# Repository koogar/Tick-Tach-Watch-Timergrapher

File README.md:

## Tick-Tach: A DIY Timegrapher for Watch Enthusiasts - TallmanLabs 2025

  Mechanical watches may seem timeless, but keeping them accurate requires precise adjustment. That’s where a timegrapher comes in. Traditionally a tool for professional watchmakers, a timegrapher measures the tiny variations in a watch’s ticking to reveal how well its movement is performing.

%20(Large).jpg)
%20(Large).jpg)

## What a Timegrapher Does

At its core, a timegrapher listens to the tick-tock of a mechanical watch and turns that sound into data. The key readings are:

  * Rate – how many seconds the watch gains or loses per day.

  * Amplitude – the swing of the balance wheel, an indicator of movement power.

  * Beat Error – how evenly spaced the tick and tock are, showing whether the balance is centred.

  Together, these measurements tell whether a watch is healthy, in need of regulation, or due for service.

https://github.com/user-attachments/assets/4d9fce35-94cd-408c-842e-20433776a29b

## The Tick-Tach Approach

  Tick-Tach is a DIY project that recreates the essential functions of a timegrapher using simple, accessible parts. Instead of an expensive acoustic sensor, Tick-Tach relies on a 30mm piezo electric microphone to detect the faint vibrations of a watch. The weak signal is amplified with a transistor-based preamp before being processed into meaningful timing data.

  Unlike commercial probes, Tick-Tach’s electronics are housed in a custom 3D-printed enclosure. The case (shown above) is designed with a circular recess for the watch to rest on, a cavity for the 30mm piezo sensor, a neatly integrated preamp board, and a headphone-style jack for easy connection. A small toggle switch adds convenience. A hair bobble is integrated into the case to retain the watch when rotating, during different position tests.

Tick-Tach is also software compatible, working with the open-source “tg-timer”, "PC Timer Machine" application on PC and the "Watch Accuracy Meter" app on Android. This allows users to visualise live waveforms, track performance, and adjust their watches using the platform they prefer.

## Why It Matters

  For hobbyists, modders, and independent watch repairers, commercial timegraphers can be costly. Tick-Tach lowers the barrier, offering enthusiasts a practical way to check accuracy, regulate their watches, and better understand the mechanics inside. It’s also a rewarding build for anyone into electronics, 3D printing, and horology.

With its smart enclosure and open-source software compatibility, Tick-Tach bridges the gap between professional watchmaking tools and the DIY workshop.

.png)

%20(Large).jpg)

%20(Large).jpg)

%20(Large).jpg)

## Technical Notes & Tips

* Apple device compatibility: Some iPhones expect a load on the microphone input of the TRRS socket. A 10 kΩ resistor between ground and mic output may be needed to “wake” the input. In some cases, mic and ground may also be reversed on the connector.

* Mono signal: The piezo pickup is mono, but this makes no difference to the timegrapher’s performance, since the software only needs a single channel of clean input. Using a standard TRRS mic/headphones adaptor may present it as dual mono, but in practice the analysis works the same.

* Piezo pickup behaviour: Unlike air microphones, the piezo disc works mainly by sensing vibration transmitted through contact with the watch case. The downside is that piezo sensors are very microphonic — they can pick up knocks, cable movement, or handling noise, so careful placement and housing design help reduce unwanted signals.

## Why Tick-Tach Stands Out

* Affordable yet accurate: Avoids the cost of commercial timegraphers while delivering reliable data.

* Open-source friendly: Works with the tg software on PC and Watch Accuracy Meter on Android for versatile use.

* Maker-centric UX: 3D-printed housing, component-level transparency, and customization potential.

* Educational and empowering: A practical electronics, signal-processing, and horology project that helps build understanding while enabling real diagnostic capability.

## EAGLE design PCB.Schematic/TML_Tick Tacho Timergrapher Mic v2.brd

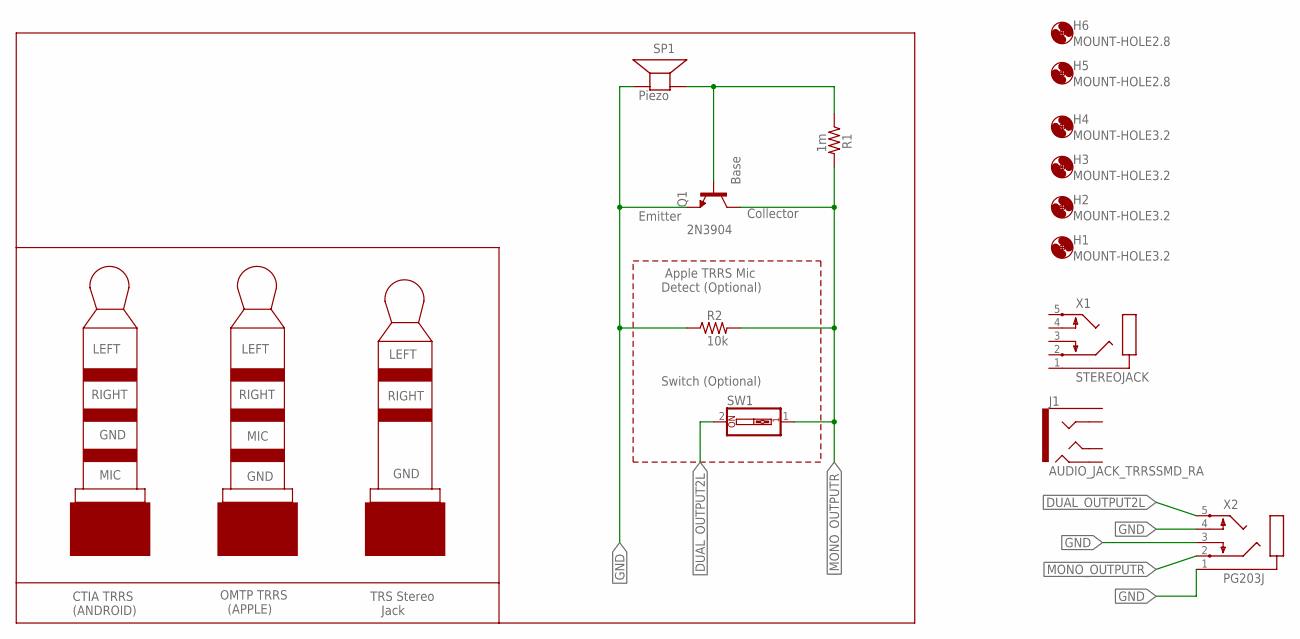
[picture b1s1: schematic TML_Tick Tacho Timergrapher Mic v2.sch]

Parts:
H1, H2, H3, H4: MOUNT-HOLE3.2; 3,2
H5, H6: MOUNT-HOLE2.8; 2,8
J1: AUDIO_JACK_TRRSSMD_RA; AUDIO_JACK_3.5MM_TRRS_SMD_RA
Q1: 2N3904; TO92
R1: 1m; 0204/7
R2: 10k; 0204/7
SP1: Piezo; AL60P
SW1: SW_DIP-1; EDG-01
X1: STEREOJACK; STX3100
X2: PG203J

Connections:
DUAL_OUTPUT2L: SW1.2, X2.5
GND: Q1.3 (E), R2.1, SP1.1 (+), X2.1, X2.3, X2.4
MONO_OUTPUTR: Q1.1 (C), R1.2, R2.2, SW1.1, X2.2
unnamed: Q1.2 (B), R1.1, SP1.2 (-)

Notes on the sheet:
Emitter
Collector
Base
Piezo
Apple TRRS Mic Detect (Optional)
MIC
GND
RIGHT
LEFT
CTIA TRRS (ANDROID)
OMTP TRRS (APPLE)
TRS Stereo Jack
Switch (Optional)

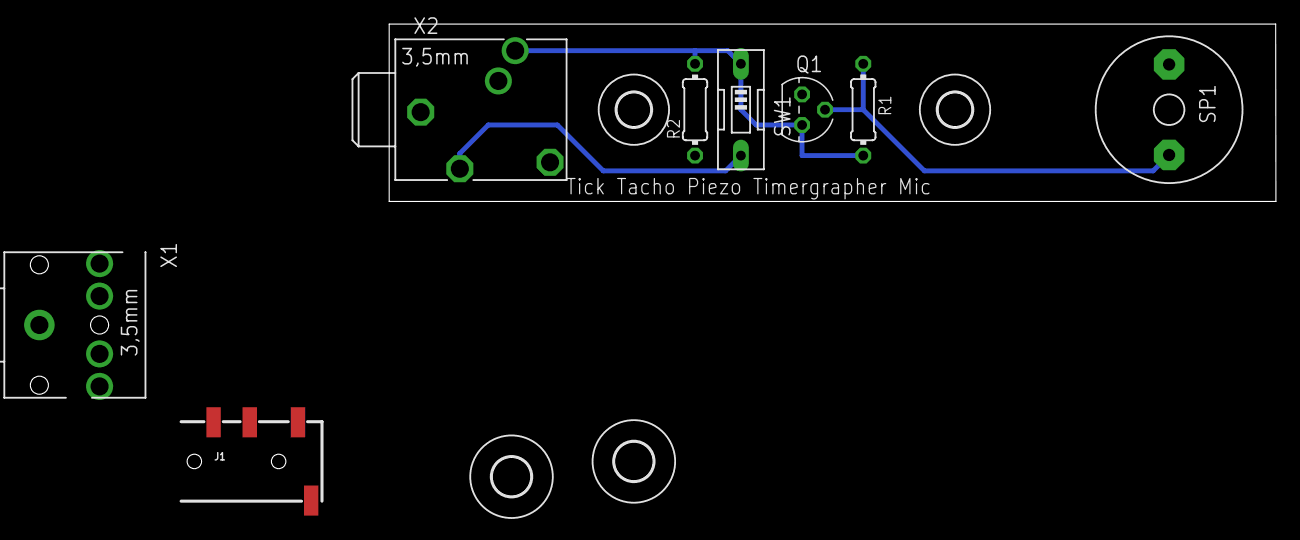
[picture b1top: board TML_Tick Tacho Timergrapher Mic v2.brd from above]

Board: 2 copper layers, 73.6 x 14.7 mm, 14 parts (0 on the bottom side), 4 nets.

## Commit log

2025-08-17 Initial
2025-08-17 upload v2 3dprint
2025-08-17 add stl
2025-08-17 add dirs
2025-08-18 update mp3

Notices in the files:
parts and their libraries:
SparkFun-Connectors: Licensing: Creative Commons ShareAlike 4.0 International - https://creativecommons.org/licenses/by-sa/4.0
